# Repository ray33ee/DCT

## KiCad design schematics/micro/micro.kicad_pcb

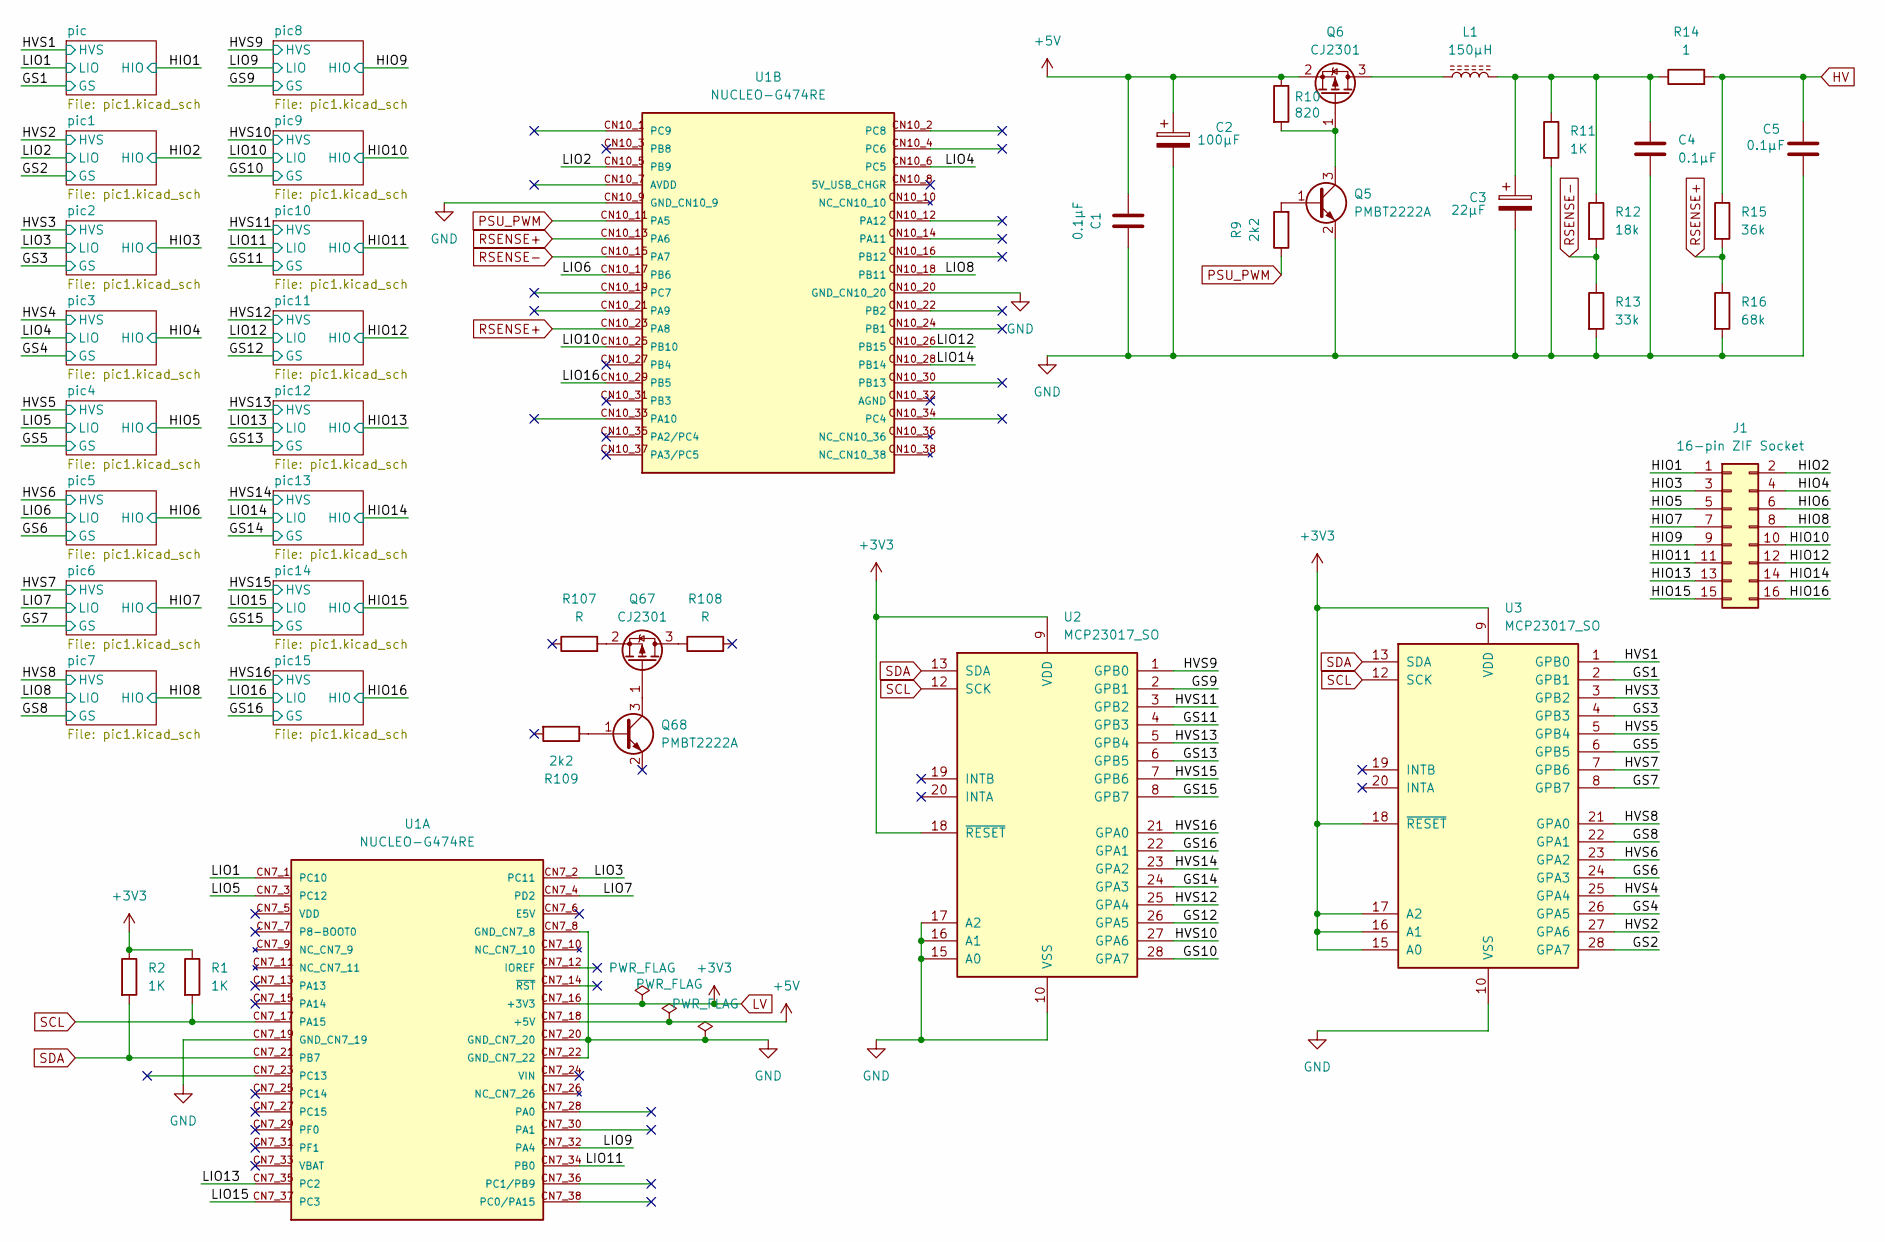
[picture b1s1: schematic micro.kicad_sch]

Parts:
C1, C4, C5: 0.1µF; C_1206_3216Metric_Pad1.33x1.80mm_HandSolder
C2: 100µF; CP_Elec_6.3x7.7
C3: 22µF; CP_Elec_6.3x5.4
J1: 16-pin ZIF Socket; ZIF-16
L1: 150µH; L_Axial_L11.0mm_D4.5mm_P15.24mm_Horizontal_Fastron_MECC
Q5, Q68: PMBT2222A; SOT-23
Q6, Q67: CJ2301; SOT-23
R1, R2, R11: 1K; R_1206_3216Metric_Pad1.30x1.75mm_HandSolder
R9, R109: 2k2; R_1206_3216Metric_Pad1.30x1.75mm_HandSolder
R10: 820; R_1206_3216Metric_Pad1.30x1.75mm_HandSolder
R12: 18k; R_1206_3216Metric_Pad1.30x1.75mm_HandSolder
R13: 33k; R_1206_3216Metric_Pad1.30x1.75mm_HandSolder
R14: 1; R_1206_3216Metric_Pad1.30x1.75mm_HandSolder
R15: 36k; R_1206_3216Metric_Pad1.30x1.75mm_HandSolder
R16: 68k; R_1206_3216Metric_Pad1.30x1.75mm_HandSolder
R107, R108: R; R_1206_3216Metric_Pad1.30x1.75mm_HandSolder
U1: NUCLEO-G474RE; G474; PARTREV 17; DigiKey_Part_Number 497-19491-ND
U2, U3: MCP23017_SO; SOIC-28W_7.5x17.9mm_P1.27mm

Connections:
+5V: C1.2, C2.1, Q6.2 (S), R10.1, U1.CN7_18 (+5V)
/GS1: U3.2 (GPB1); also elsewhere on the board
/GS2: U3.28 (GPA7); also elsewhere on the board
/GS3: U3.4 (GPB3); also elsewhere on the board
/GS4: U3.26 (GPA5); also elsewhere on the board
/GS5: U3.6 (GPB5); also elsewhere on the board
/GS6: U3.24 (GPA3); also elsewhere on the board
/GS7: U3.8 (GPB7); also elsewhere on the board
/GS8: U3.22 (GPA1); also elsewhere on the board
/GS9: U2.2 (GPB1); also elsewhere on the board
/GS10: U2.28 (GPA7); also elsewhere on the board
/GS11: U2.4 (GPB3); also elsewhere on the board
/GS12: U2.26 (GPA5); also elsewhere on the board
/GS13: U2.6 (GPB5); also elsewhere on the board
/GS14: U2.24 (GPA3); also elsewhere on the board
/GS15: U2.8 (GPB7); also elsewhere on the board
/GS16: U2.22 (GPA1); also elsewhere on the board
/HIO1: J1.1; also elsewhere on the board
/HIO2: J1.2; also elsewhere on the board
/HIO3: J1.3; also elsewhere on the board
/HIO4: J1.4; also elsewhere on the board
/HIO5: J1.5; also elsewhere on the board
/HIO6: J1.6; also elsewhere on the board
/HIO7: J1.7; also elsewhere on the board
/HIO8: J1.8; also elsewhere on the board
/HIO9: J1.9; also elsewhere on the board
/HIO10: J1.10; also elsewhere on the board
/HIO11: J1.11; also elsewhere on the board
/HIO12: J1.12; also elsewhere on the board
/HIO13: J1.13; also elsewhere on the board
/HIO14: J1.14; also elsewhere on the board
/HIO15: J1.15; also elsewhere on the board
/HIO16: J1.16; also elsewhere on the board
/HVS1: U3.1 (GPB0); also elsewhere on the board
/HVS2: U3.27 (GPA6); also elsewhere on the board
/HVS3: U3.3 (GPB2); also elsewhere on the board
/HVS4: U3.25 (GPA4); also elsewhere on the board
/HVS5: U3.5 (GPB4); also elsewhere on the board
/HVS6: U3.23 (GPA2); also elsewhere on the board
/HVS7: U3.7 (GPB6); also elsewhere on the board
/HVS8: U3.21 (GPA0); also elsewhere on the board
/HVS9: U2.1 (GPB0); also elsewhere on the board
/HVS10: U2.27 (GPA6); also elsewhere on the board
/HVS11: U2.3 (GPB2); also elsewhere on the board
/HVS12: U2.25 (GPA4); also elsewhere on the board
/HVS13: U2.5 (GPB4); also elsewhere on the board
/HVS14: U2.23 (GPA2); also elsewhere on the board
/HVS15: U2.7 (GPB6); also elsewhere on the board
/HVS16: U2.21 (GPA0); also elsewhere on the board
/LIO1: U1.CN7_1 (PC10); also elsewhere on the board
/LIO2: U1.CN10_5 (PB9); also elsewhere on the board
/LIO3: U1.CN7_2 (PC11); also elsewhere on the board
/LIO4: U1.CN10_6 (PC5); also elsewhere on the board
/LIO5: U1.CN7_3 (PC12); also elsewhere on the board
/LIO6: U1.CN10_17 (PB6); also elsewhere on the board
/LIO7: U1.CN7_4 (PD2); also elsewhere on the board
/LIO8: U1.CN10_18 (PB11); also elsewhere on the board
/LIO9: U1.CN7_32 (PA4); also elsewhere on the board
/LIO10: U1.CN10_25 (PB10); also elsewhere on the board
/LIO11: U1.CN7_34 (PB0); also elsewhere on the board
/LIO12: U1.CN10_26 (PB15); also elsewhere on the board
/LIO13: U1.CN7_35 (PC2); also elsewhere on the board
/LIO14: U1.CN10_28 (PB14); also elsewhere on the board
/LIO15: U1.CN7_37 (PC3); also elsewhere on the board
/LIO16: U1.CN10_29 (PB5); also elsewhere on the board
GND: C1.1, C2.2, C3.2, C4.2, C5.2, Q5.2 (E), R11.2, R13.2, R16.2, U1.CN7_8 (GND_CN7_8), U1.CN7_19 (GND_CN7_19), U1.CN7_20 (GND_CN7_20), U1.CN7_22 (GND_CN7_22), U1.CN10_9 (GND_CN10_9), U1.CN10_20 (GND_CN10_20), U2.10 (VSS), U2.15 (A0), U2.16 (A1), U2.17 (A2), U3.10 (VSS); also elsewhere on the board
HV: C5.1, R14.2, R15.1; also elsewhere on the board
LV: R1.1, R2.1, U1.CN7_16 (+3V3), U2.9 (VDD), U2.18 (~RESET), U3.9 (VDD), U3.15 (A0), U3.16 (A1), U3.17 (A2), U3.18 (~RESET); also elsewhere on the board
unnamed: C3.1, C4.1, L1.2, R11.1, R12.1, R14.1
unnamed: Q5.1 (B), R9.2
unnamed: Q5.3 (C), Q6.1 (G), R10.2
unnamed: L1.1, Q6.3 (D)
unnamed: Q67.3 (D), R108.1
unnamed: Q67.1 (G), Q68.3 (C)
unnamed: Q67.2 (S), R107.2
unnamed: Q68.1 (B), R109.1
PSU_PWM: R9.1, U1.CN10_11 (PA5)
RSENSE+: R15.2, R16.1, U1.CN10_13 (PA6), U1.CN10_23 (PA8)
RSENSE-: R12.2, R13.1, U1.CN10_15 (PA7)
SCL: R1.2, U1.CN7_17 (PA15), U2.12 (SCK), U3.12 (SCK)
SDA: R2.2, U1.CN7_21 (PB7), U2.13 (SDA), U3.13 (SDA)

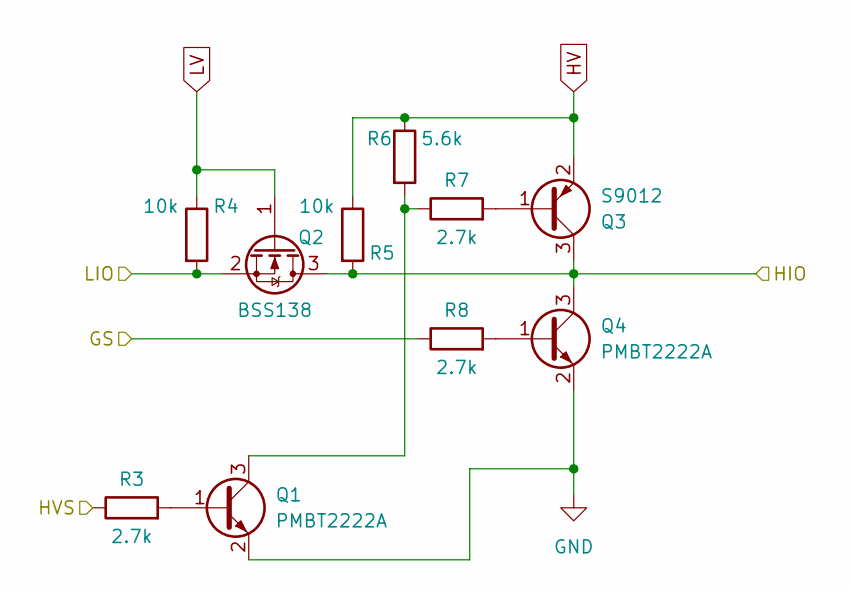
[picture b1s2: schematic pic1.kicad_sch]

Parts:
Q1, Q4: PMBT2222A; SOT-23_Handsoldering
Q2: BSS138; SOT-23_Handsoldering
Q3: S9012; SOT-23_Handsoldering
R3, R7, R8: 2.7k; R_1206_3216Metric_Pad1.30x1.75mm_HandSolder
R4, R5: 10k; R_1206_3216Metric_Pad1.30x1.75mm_HandSolder
R6: 5.6k; R_1206_3216Metric_Pad1.30x1.75mm_HandSolder

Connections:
/GS1: R8.1; also elsewhere on the board
/HIO1: Q2.3 (D), Q3.3 (C), Q4.3 (C), R5.2; also elsewhere on the board
/HVS1: R3.1; also elsewhere on the board
/LIO1: Q2.2 (S), R4.2; also elsewhere on the board
GND: Q1.2 (E), Q4.2 (E); also elsewhere on the board
HV: Q3.2 (E), R5.1, R6.1; also elsewhere on the board
LV: Q2.1 (G), R4.1; also elsewhere on the board
unnamed: Q1.1 (B), R3.2
unnamed: Q1.3 (C), R6.2, R7.1
unnamed: Q3.1 (B), R7.2
unnamed: Q4.1 (B), R8.2

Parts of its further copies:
Q7, Q10, Q11, Q14, Q15, Q18, Q19, Q22, Q23, Q26, Q27, Q30, Q31, Q34, Q35, Q38, Q39, Q42, Q43, Q46, Q47, Q50, Q51, Q54, Q55, Q58, Q59, Q62, Q63, Q66: PMBT2222A; SOT-23_Handsoldering
Q8, Q12, Q16, Q20, Q24, Q28, Q32, Q36, Q40, Q44, Q48, Q52, Q56, Q60, Q64: BSS138; SOT-23_Handsoldering
Q9, Q13, Q17, Q21, Q25, Q29, Q33, Q37, Q41, Q45, Q49, Q53, Q57, Q61, Q65: S9012; SOT-23_Handsoldering
R17, R21, R22, R23, R27, R28, R29, R33, R34, R35, R39, R40, R41, R45, R46, R47, R51, R52, R53, R57, R58, R59, R63, R64, R65, R69, R70, R71, R75, R76, R77, R81, R82, R83, R87, R88, R89, R93, R94, R95, R99, R100, R101, R105, R106: 2.7k; R_1206_3216Metric_Pad1.30x1.75mm_HandSolder
R18, R19, R24, R25, R30, R31, R36, R37, R42, R43, R48, R49, R54, R55, R60, R61, R66, R67, R72, R73, R78, R79, R84, R85, R90, R91, R96, R97, R102, R103: 10k; R_1206_3216Metric_Pad1.30x1.75mm_HandSolder
R20, R26, R32, R38, R44, R50, R56, R62, R68, R74, R80, R86, R92, R98, R104: 5.6k; R_1206_3216Metric_Pad1.30x1.75mm_HandSolder

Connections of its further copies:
/GS2: R22.1; also elsewhere on the board
/GS3: R28.1; also elsewhere on the board
/GS4: R34.1; also elsewhere on the board
/GS5: R40.1; also elsewhere on the board
/GS6: R46.1; also elsewhere on the board
/GS7: R52.1; also elsewhere on the board
/GS8: R58.1; also elsewhere on the board
/GS9: R64.1; also elsewhere on the board
/GS10: R70.1; also elsewhere on the board
/GS11: R76.1; also elsewhere on the board
/GS12: R82.1; also elsewhere on the board
/GS13: R88.1; also elsewhere on the board
/GS14: R94.1; also elsewhere on the board
/GS15: R100.1; also elsewhere on the board
/GS16: R106.1; also elsewhere on the board
/HIO2: Q8.3 (D), Q9.3 (C), Q10.3 (C), R19.2; also elsewhere on the board
/HIO3: Q12.3 (D), Q13.3 (C), Q14.3 (C), R25.2; also elsewhere on the board
/HIO4: Q16.3 (D), Q17.3 (C), Q18.3 (C), R31.2; also elsewhere on the board
/HIO5: Q20.3 (D), Q21.3 (C), Q22.3 (C), R37.2; also elsewhere on the board
/HIO6: Q24.3 (D), Q25.3 (C), Q26.3 (C), R43.2; also elsewhere on the board
/HIO7: Q28.3 (D), Q29.3 (C), Q30.3 (C), R49.2; also elsewhere on the board
/HIO8: Q32.3 (D), Q33.3 (C), Q34.3 (C), R55.2; also elsewhere on the board
/HIO9: Q36.3 (D), Q37.3 (C), Q38.3 (C), R61.2; also elsewhere on the board
/HIO10: Q40.3 (D), Q41.3 (C), Q42.3 (C), R67.2; also elsewhere on the board
/HIO11: Q44.3 (D), Q45.3 (C), Q46.3 (C), R73.2; also elsewhere on the board
/HIO12: Q48.3 (D), Q49.3 (C), Q50.3 (C), R79.2; also elsewhere on the board
/HIO13: Q52.3 (D), Q53.3 (C), Q54.3 (C), R85.2; also elsewhere on the board
/HIO14: Q56.3 (D), Q57.3 (C), Q58.3 (C), R91.2; also elsewhere on the board
/HIO15: Q60.3 (D), Q61.3 (C), Q62.3 (C), R97.2; also elsewhere on the board
/HIO16: Q64.3 (D), Q65.3 (C), Q66.3 (C), R103.2; also elsewhere on the board
/HVS2: R17.1; also elsewhere on the board
/HVS3: R23.1; also elsewhere on the board
/HVS4: R29.1; also elsewhere on the board
/HVS5: R35.1; also elsewhere on the board
/HVS6: R41.1; also elsewhere on the board
/HVS7: R47.1; also elsewhere on the board
/HVS8: R53.1; also elsewhere on the board
/HVS9: R59.1; also elsewhere on the board
/HVS10: R65.1; also elsewhere on the board
/HVS11: R71.1; also elsewhere on the board
/HVS12: R77.1; also elsewhere on the board
/HVS13: R83.1; also elsewhere on the board
/HVS14: R89.1; also elsewhere on the board
/HVS15: R95.1; also elsewhere on the board
/HVS16: R101.1; also elsewhere on the board
/LIO2: Q8.2 (S), R18.2; also elsewhere on the board
/LIO3: Q12.2 (S), R24.2; also elsewhere on the board
/LIO4: Q16.2 (S), R30.2; also elsewhere on the board
/LIO5: Q20.2 (S), R36.2; also elsewhere on the board
/LIO6: Q24.2 (S), R42.2; also elsewhere on the board
/LIO7: Q28.2 (S), R48.2; also elsewhere on the board
/LIO8: Q32.2 (S), R54.2; also elsewhere on the board
/LIO9: Q36.2 (S), R60.2; also elsewhere on the board
/LIO10: Q40.2 (S), R66.2; also elsewhere on the board
/LIO11: Q44.2 (S), R72.2; also elsewhere on the board
/LIO12: Q48.2 (S), R78.2; also elsewhere on the board
/LIO13: Q52.2 (S), R84.2; also elsewhere on the board
/LIO14: Q56.2 (S), R90.2; also elsewhere on the board
/LIO15: Q60.2 (S), R96.2; also elsewhere on the board
/LIO16: Q64.2 (S), R102.2; also elsewhere on the board
GND: Q7.2 (E), Q10.2 (E), Q11.2 (E), Q14.2 (E), Q15.2 (E), Q18.2 (E), Q19.2 (E), Q22.2 (E), Q23.2 (E), Q26.2 (E), Q27.2 (E), Q30.2 (E), Q31.2 (E), Q34.2 (E), Q35.2 (E), Q38.2 (E), Q39.2 (E), Q42.2 (E), Q43.2 (E), Q46.2 (E), Q47.2 (E), Q50.2 (E), Q51.2 (E), Q54.2 (E), Q55.2 (E), Q58.2 (E), Q59.2 (E), Q62.2 (E), Q63.2 (E), Q66.2 (E); also elsewhere on the board
HV: Q9.2 (E), Q13.2 (E), Q17.2 (E), Q21.2 (E), Q25.2 (E), Q29.2 (E), Q33.2 (E), Q37.2 (E), Q41.2 (E), Q45.2 (E), Q49.2 (E), Q53.2 (E), Q57.2 (E), Q61.2 (E), Q65.2 (E), R19.1, R20.1, R25.1, R26.1, R31.1, R32.1, R37.1, R38.1, R43.1, R44.1, R49.1, R50.1, R55.1, R56.1, R61.1, R62.1, R67.1, R68.1, R73.1, R74.1, R79.1, R80.1, R85.1, R86.1, R91.1, R92.1, R97.1, R98.1, R103.1, R104.1; also elsewhere on the board
LV: Q8.1 (G), Q12.1 (G), Q16.1 (G), Q20.1 (G), Q24.1 (G), Q28.1 (G), Q32.1 (G), Q36.1 (G), Q40.1 (G), Q44.1 (G), Q48.1 (G), Q52.1 (G), Q56.1 (G), Q60.1 (G), Q64.1 (G), R18.1, R24.1, R30.1, R36.1, R42.1, R48.1, R54.1, R60.1, R66.1, R72.1, R78.1, R84.1, R90.1, R96.1, R102.1; also elsewhere on the board
unnamed: Q7.1 (B), R17.2
unnamed: Q7.3 (C), R20.2, R21.1
unnamed: Q9.1 (B), R21.2
unnamed: Q10.1 (B), R22.2
unnamed: Q11.1 (B), R23.2
unnamed: Q11.3 (C), R26.2, R27.1
unnamed: Q13.1 (B), R27.2
unnamed: Q14.1 (B), R28.2
unnamed: Q15.1 (B), R29.2
unnamed: Q15.3 (C), R32.2, R33.1
unnamed: Q17.1 (B), R33.2
unnamed: Q18.1 (B), R34.2
unnamed: Q19.1 (B), R35.2
unnamed: Q19.3 (C), R38.2, R39.1
unnamed: Q21.1 (B), R39.2
unnamed: Q22.1 (B), R40.2
unnamed: Q23.1 (B), R41.2
unnamed: Q23.3 (C), R44.2, R45.1
unnamed: Q25.1 (B), R45.2
unnamed: Q26.1 (B), R46.2
unnamed: Q27.1 (B), R47.2
unnamed: Q27.3 (C), R50.2, R51.1
unnamed: Q29.1 (B), R51.2
unnamed: Q30.1 (B), R52.2
unnamed: Q31.1 (B), R53.2
unnamed: Q31.3 (C), R56.2, R57.1
unnamed: Q33.1 (B), R57.2
unnamed: Q34.1 (B), R58.2
unnamed: Q35.1 (B), R59.2
unnamed: Q35.3 (C), R62.2, R63.1
unnamed: Q37.1 (B), R63.2
unnamed: Q38.1 (B), R64.2
unnamed: Q39.1 (B), R65.2
unnamed: Q39.3 (C), R68.2, R69.1
unnamed: Q41.1 (B), R69.2
unnamed: Q42.1 (B), R70.2
unnamed: Q43.1 (B), R71.2
unnamed: Q43.3 (C), R74.2, R75.1
unnamed: Q45.1 (B), R75.2
unnamed: Q46.1 (B), R76.2
unnamed: Q47.1 (B), R77.2
unnamed: Q47.3 (C), R80.2, R81.1
unnamed: Q49.1 (B), R81.2
unnamed: Q50.1 (B), R82.2
unnamed: Q51.1 (B), R83.2
unnamed: Q51.3 (C), R86.2, R87.1
unnamed: Q53.1 (B), R87.2
unnamed: Q54.1 (B), R88.2
unnamed: Q55.1 (B), R89.2
unnamed: Q55.3 (C), R92.2, R93.1
unnamed: Q57.1 (B), R93.2
unnamed: Q58.1 (B), R94.2
unnamed: Q59.1 (B), R95.2
unnamed: Q59.3 (C), R98.2, R99.1
unnamed: Q61.1 (B), R99.2
unnamed: Q62.1 (B), R100.2
unnamed: Q63.1 (B), R101.2
unnamed: Q63.3 (C), R104.2, R105.1
unnamed: Q65.1 (B), R105.2
unnamed: Q66.1 (B), R106.2

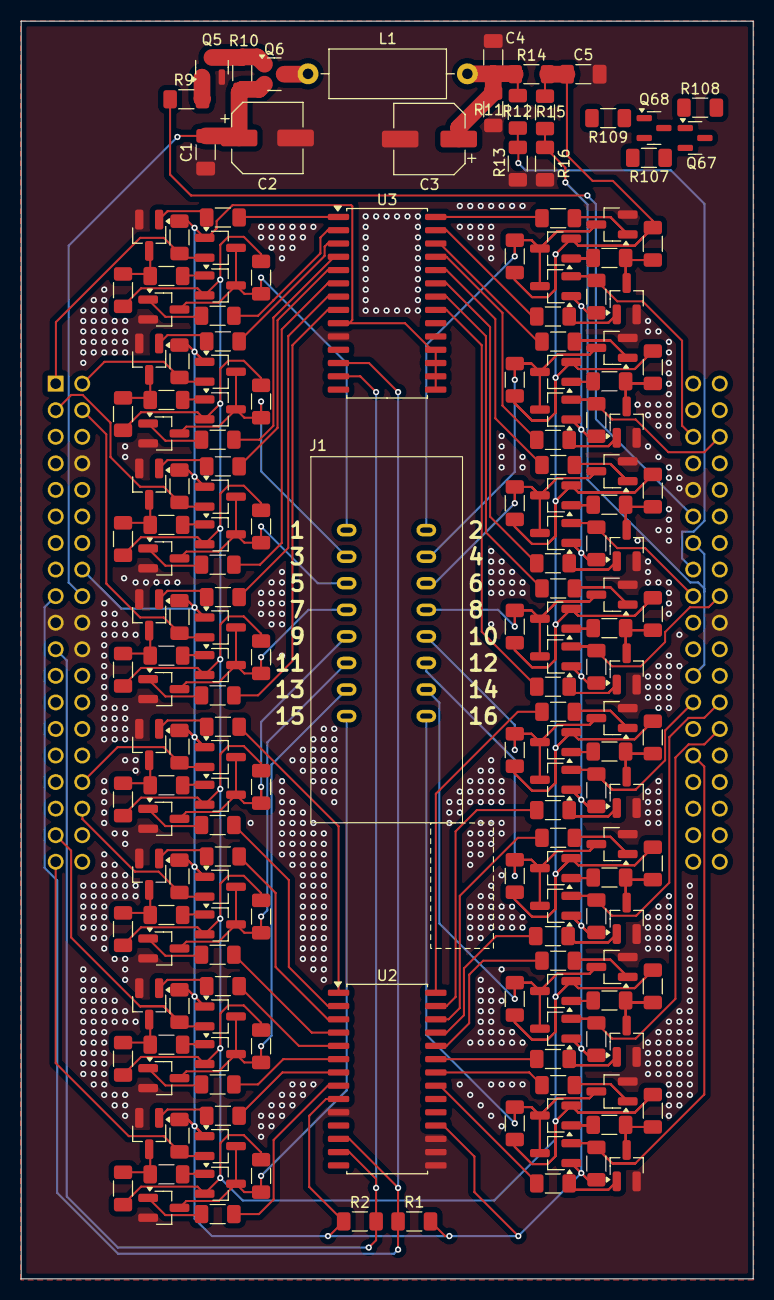
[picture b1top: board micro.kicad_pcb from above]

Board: 2 copper layers, 70.0 x 120.3 mm, 187 parts (0 on the bottom side), 145 nets.

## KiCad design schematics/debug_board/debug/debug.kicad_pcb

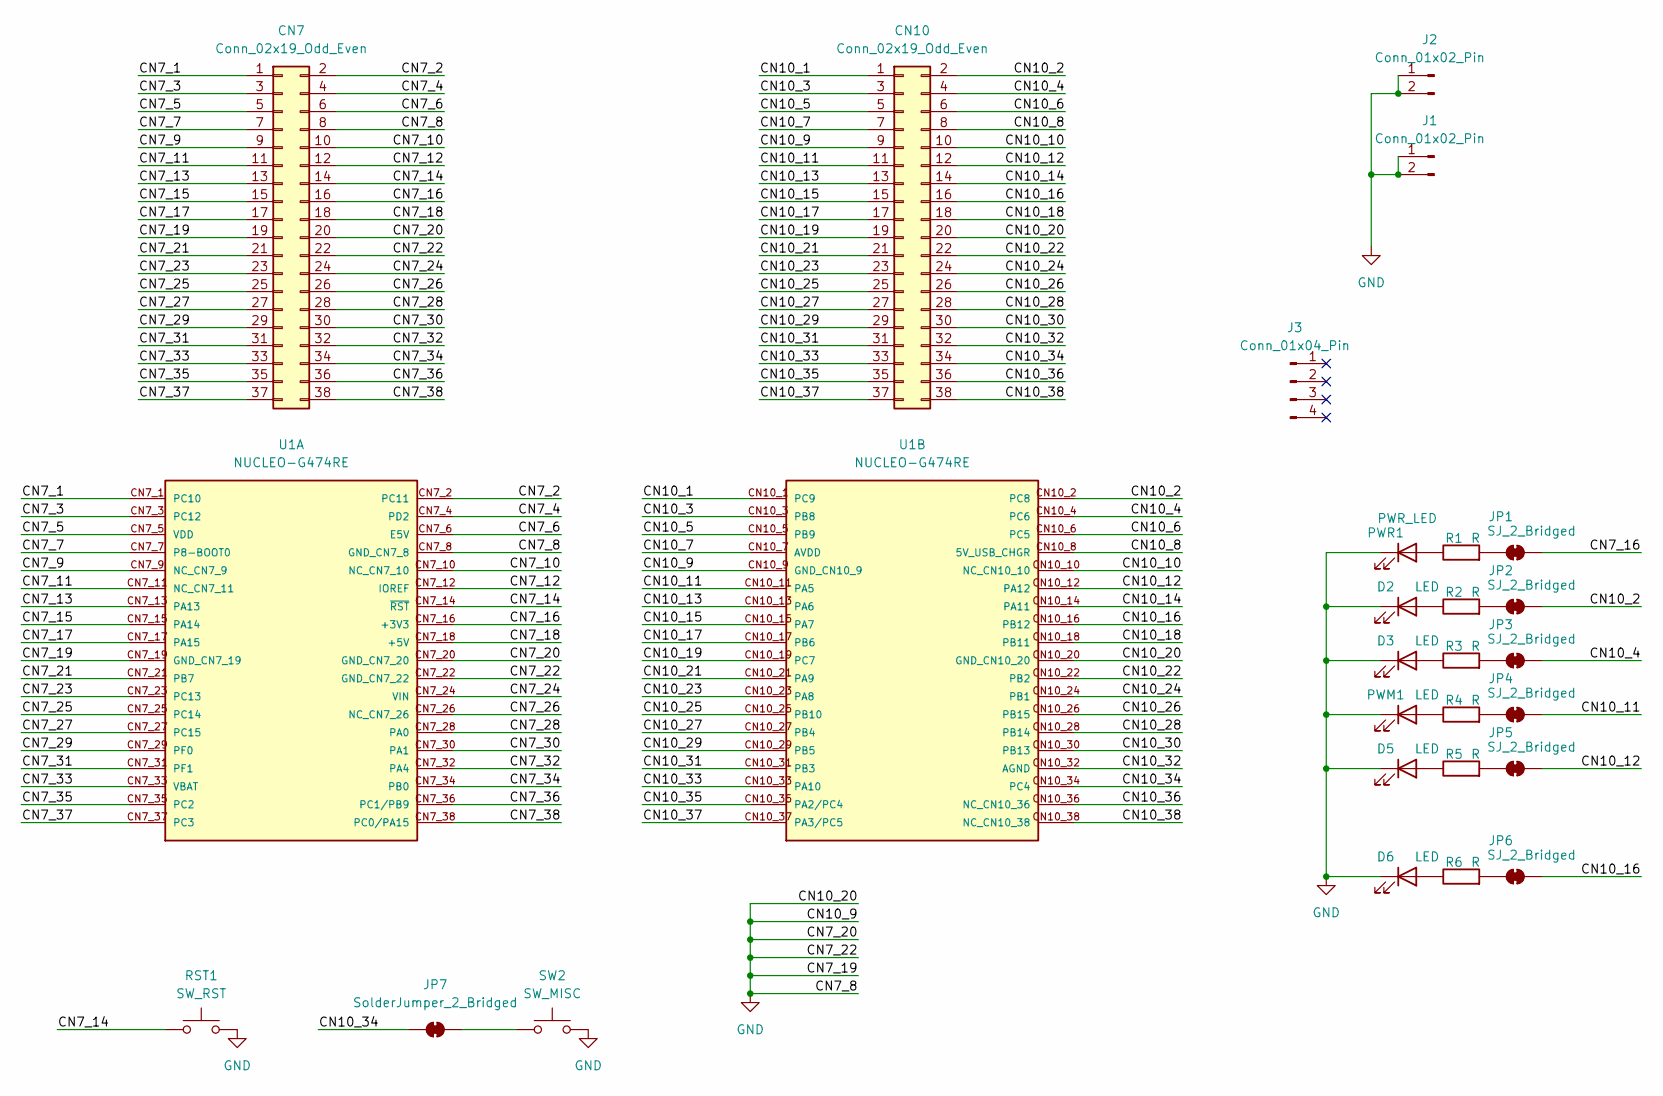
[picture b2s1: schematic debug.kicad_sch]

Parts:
CN7, CN10: Conn_02x19_Odd_Even; PinHeader_2x19_P2.54mm_Vertical
D2, D3, D5, D6: LED; LED_1206_3216Metric_Pad1.42x1.75mm_HandSolder
J1, J2: Conn_01x02_Pin; PinHeader_2x01_P2.54mm_Vertical
J3: Conn_01x04_Pin; PinHeader_1x04_P2.54mm_Vertical
JP1, JP2, JP3, JP4, JP5, JP6: SJ_2_Bridged; SolderJumper-2_P1.3mm_Bridged_RoundedPad1.0x1.5mm
JP7: SolderJumper_2_Bridged; SolderJumper-2_P1.3mm_Bridged_RoundedPad1.0x1.5mm
PWM1: LED; LED_1206_3216Metric_Pad1.42x1.75mm_HandSolder
PWR1: PWR_LED; LED_1206_3216Metric_Pad1.42x1.75mm_HandSolder
R1, R2, R3, R4, R5, R6: R; R_1206_3216Metric_Pad1.30x1.75mm_HandSolder
RST1: SW_RST; SW_SPST_FSMSM
SW2: SW_MISC; SW_SPST_FSMSM
U1: NUCLEO-G474RE; G474; PARTREV 17; DigiKey_Part_Number 497-19491-ND

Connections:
/CN7_1: CN7.1, U1.CN7_1 (PC10)
/CN7_2: CN7.2, U1.CN7_2 (PC11)
/CN7_3: CN7.3, U1.CN7_3 (PC12)
/CN7_4: CN7.4, U1.CN7_4 (PD2)
/CN7_5: CN7.5, U1.CN7_5 (VDD)
/CN7_6: CN7.6, U1.CN7_6 (E5V)
/CN7_7: CN7.7, U1.CN7_7 (P8-BOOT0)
/CN7_9: CN7.9, U1.CN7_9 (NC_CN7_9)
/CN7_10: CN7.10, U1.CN7_10 (NC_CN7_10)
/CN7_11: CN7.11, U1.CN7_11 (NC_CN7_11)
/CN7_12: CN7.12, U1.CN7_12 (IOREF)
/CN7_13: CN7.13, U1.CN7_13 (PA13)
/CN7_14: CN7.14, RST1.1, U1.CN7_14 (~RST)
/CN7_15: CN7.15, U1.CN7_15 (PA14)
/CN7_16: CN7.16, JP1.2 (B), U1.CN7_16 (+3V3)
/CN7_17: CN7.17, U1.CN7_17 (PA15)
/CN7_18: CN7.18, U1.CN7_18 (+5V)
/CN7_21: CN7.21, U1.CN7_21 (PB7)
/CN7_23: CN7.23, U1.CN7_23 (PC13)
/CN7_24: CN7.24, U1.CN7_24 (VIN)
/CN7_25: CN7.25, U1.CN7_25 (PC14)
/CN7_26: CN7.26, U1.CN7_26 (NC_CN7_26)
/CN7_27: CN7.27, U1.CN7_27 (PC15)
/CN7_28: CN7.28, U1.CN7_28 (PA0)
/CN7_29: CN7.29, U1.CN7_29 (PF0)
/CN7_30: CN7.30, U1.CN7_30 (PA1)
/CN7_31: CN7.31, U1.CN7_31 (PF1)
/CN7_32: CN7.32, U1.CN7_32 (PA4)
/CN7_33: CN7.33, U1.CN7_33 (VBAT)
/CN7_34: CN7.34, U1.CN7_34 (PB0)
/CN7_35: CN7.35, U1.CN7_35 (PC2)
/CN7_36: CN7.36, U1.CN7_36 (PC1/PB9)
/CN7_37: CN7.37, U1.CN7_37 (PC3)
/CN7_38: CN7.38, U1.CN7_38 (PC0/PA15)
/CN10_1: CN10.1, U1.CN10_1 (PC9)
/CN10_2: CN10.2, JP2.2 (B), U1.CN10_2 (PC8)
/CN10_3: CN10.3, U1.CN10_3 (PB8)
/CN10_4: CN10.4, JP3.2 (B), U1.CN10_4 (PC6)
/CN10_5: CN10.5, U1.CN10_5 (PB9)
/CN10_6: CN10.6, U1.CN10_6 (PC5)
/CN10_7: CN10.7, U1.CN10_7 (AVDD)
/CN10_8: CN10.8, U1.CN10_8 (5V_USB_CHGR)
/CN10_10: CN10.10, U1.CN10_10 (NC_CN10_10)
/CN10_11: CN10.11, JP4.2 (B), U1.CN10_11 (PA5)
/CN10_12: CN10.12, JP5.2 (B), U1.CN10_12 (PA12)
/CN10_13: CN10.13, U1.CN10_13 (PA6)
/CN10_14: CN10.14, U1.CN10_14 (PA11)
/CN10_15: CN10.15, U1.CN10_15 (PA7)
/CN10_16: CN10.16, JP6.2 (B), U1.CN10_16 (PB12)
/CN10_17: CN10.17, U1.CN10_17 (PB6)
/CN10_18: CN10.18, U1.CN10_18 (PB11)
/CN10_19: CN10.19, U1.CN10_19 (PC7)
/CN10_21: CN10.21, U1.CN10_21 (PA9)
/CN10_22: CN10.22, U1.CN10_22 (PB2)
/CN10_23: CN10.23, U1.CN10_23 (PA8)
/CN10_24: CN10.24, U1.CN10_24 (PB1)
/CN10_25: CN10.25, U1.CN10_25 (PB10)
/CN10_26: CN10.26, U1.CN10_26 (PB15)
/CN10_27: CN10.27, U1.CN10_27 (PB4)
/CN10_28: CN10.28, U1.CN10_28 (PB14)
/CN10_29: CN10.29, U1.CN10_29 (PB5)
/CN10_30: CN10.30, U1.CN10_30 (PB13)
/CN10_31: CN10.31, U1.CN10_31 (PB3)
/CN10_32: CN10.32, U1.CN10_32 (AGND)
/CN10_33: CN10.33, U1.CN10_33 (PA10)
/CN10_34: CN10.34, JP7.1 (A), U1.CN10_34 (PC4)
/CN10_35: CN10.35, U1.CN10_35 (PA2/PC4)
/CN10_36: CN10.36, U1.CN10_36 (NC_CN10_36)
/CN10_37: CN10.37, U1.CN10_37 (PA3/PC5)
/CN10_38: CN10.38, U1.CN10_38 (NC_CN10_38)
GND: CN7.8, CN7.19, CN7.20, CN7.22, CN10.9, CN10.20, D2.1 (K), D3.1 (K), D5.1 (K), D6.1 (K), J1.1, J1.2, J2.1, J2.2, PWM1.1 (K), PWR1.1 (K), RST1.2, SW2.2, U1.CN7_8 (GND_CN7_8), U1.CN7_19 (GND_CN7_19), U1.CN7_20 (GND_CN7_20), U1.CN7_22 (GND_CN7_22), U1.CN10_9 (GND_CN10_9), U1.CN10_20 (GND_CN10_20)
unnamed: D2.2 (A), R2.1
unnamed: D3.2 (A), R3.1
unnamed: D5.2 (A), R5.1
unnamed: D6.2 (A), R6.1
unnamed: JP1.1 (A), R1.2
unnamed: JP2.1 (A), R2.2
unnamed: JP3.1 (A), R3.2
unnamed: JP4.1 (A), R4.2
unnamed: JP5.1 (A), R5.2
unnamed: JP6.1 (A), R6.2
unnamed: JP7.2 (B), SW2.1
unnamed: PWM1.2 (A), R4.1
unnamed: PWR1.2 (A), R1.1

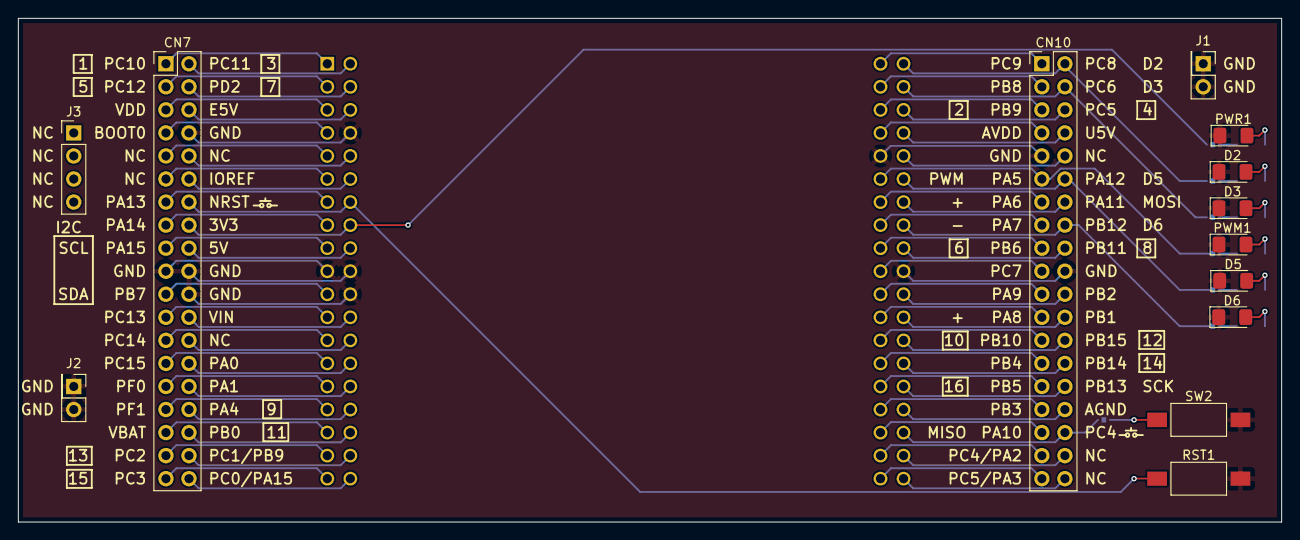
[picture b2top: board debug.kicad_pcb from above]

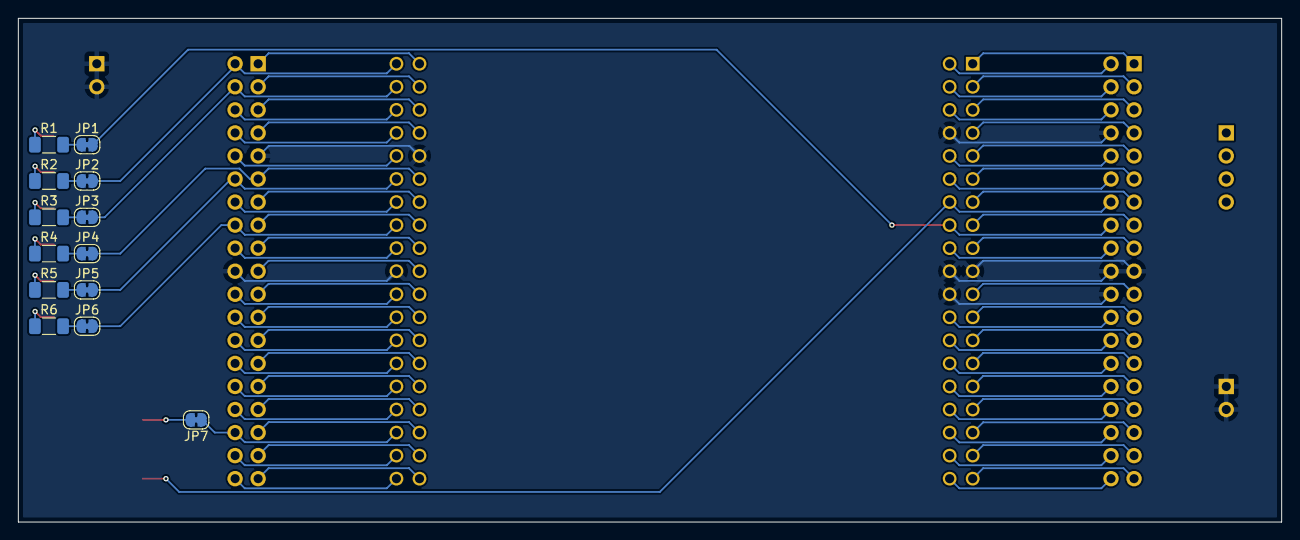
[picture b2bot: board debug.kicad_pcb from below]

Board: 2 copper layers, 139.2 x 55.5 mm, 27 parts (13 on the bottom side), 84 nets.

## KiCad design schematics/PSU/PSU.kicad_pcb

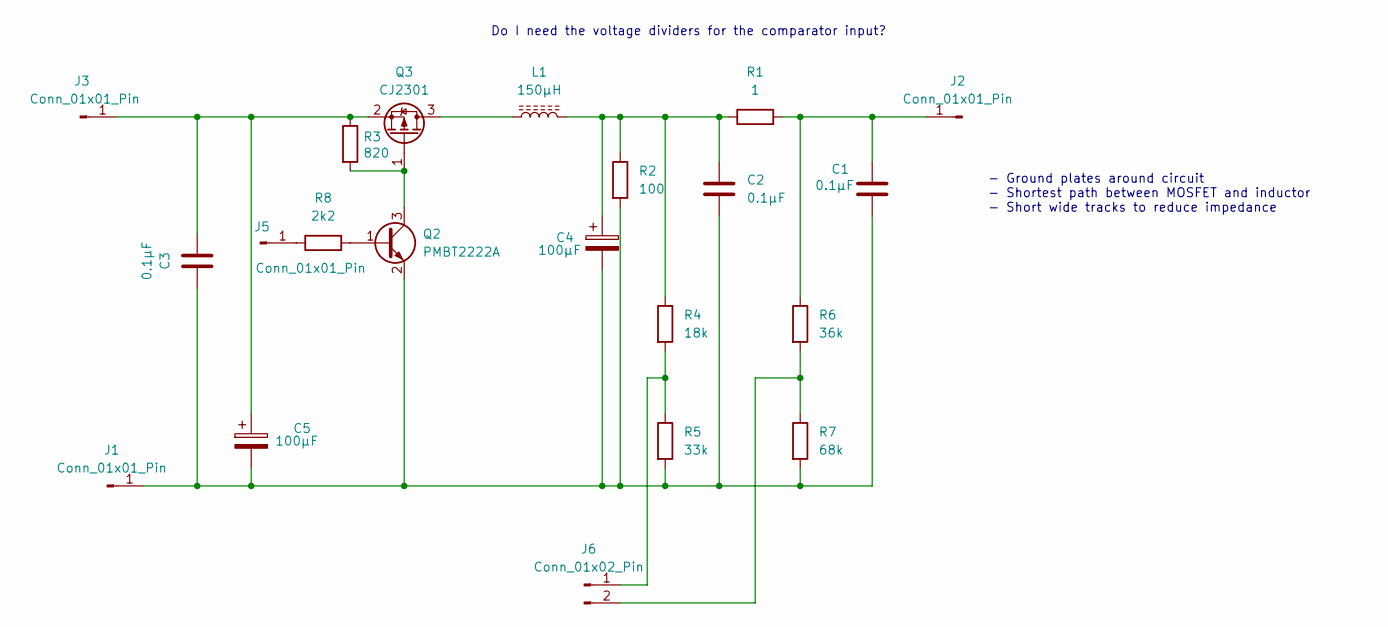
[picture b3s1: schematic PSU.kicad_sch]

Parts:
C1, C2, C3: 0.1µF; C_1206_3216Metric_Pad1.33x1.80mm_HandSolder
C4, C5: 100µF; CP_Radial_D10.0mm_P5.00mm
J1, J2, J3, J5: Conn_01x01_Pin; PinHeader_1x01_P2.54mm_Vertical
J6: Conn_01x02_Pin; PinHeader_1x02_P2.54mm_Vertical
L1: 150µH; L_Axial_L11.0mm_D4.5mm_P15.24mm_Horizontal_Fastron_MECC
Q2: PMBT2222A; SOT-23
Q3: CJ2301; SOT-23
R1: 1; R_1206_3216Metric_Pad1.30x1.75mm_HandSolder
R2: 100; R_2512_6332Metric_Pad1.40x3.35mm_HandSolder
R3: 820; R_1206_3216Metric_Pad1.30x1.75mm_HandSolder
R4: 18k; R_1206_3216Metric_Pad1.30x1.75mm_HandSolder
R5: 33k; R_1206_3216Metric_Pad1.30x1.75mm_HandSolder
R6: 36k; R_1206_3216Metric_Pad1.30x1.75mm_HandSolder
R7: 68k; R_1206_3216Metric_Pad1.30x1.75mm_HandSolder
R8: 2k2; R_1206_3216Metric_Pad1.30x1.75mm_HandSolder

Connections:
unnamed: C2.1, C4.1, L1.2, R1.1, R2.1, R4.1
unnamed: C1.2, C2.2, C3.1, C4.2, C5.2, J1.1, Q2.2 (E), R2.2, R5.2, R7.2
unnamed: C1.1, J2.1, R1.2, R6.1
unnamed: C3.2, C5.1, J3.1, Q3.2 (S), R3.1
unnamed: J5.1, R8.1
unnamed: J6.1, R4.2, R5.1
unnamed: J6.2, R6.2, R7.1
unnamed: Q2.1 (B), R8.2
unnamed: Q2.3 (C), Q3.1 (G), R3.2
unnamed: L1.1, Q3.3 (D)

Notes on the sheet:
- Ground plates around circuit - Shortest path between MOSFET and inductor - Short wide tracks to reduce impedance
Do I need the voltage dividers for the comparator input?

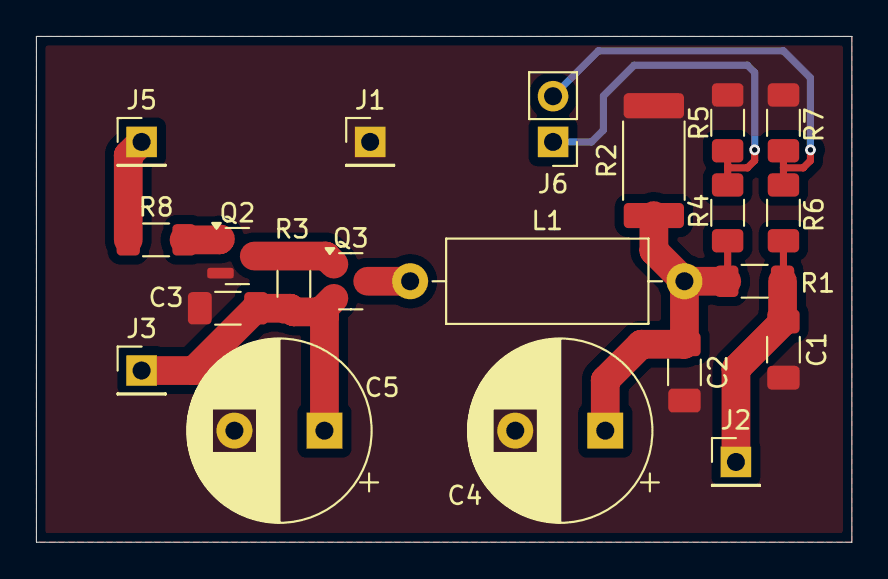
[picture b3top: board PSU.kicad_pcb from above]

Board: 2 copper layers, 45.3 x 28.1 mm, 21 parts (0 on the bottom side), 10 nets.

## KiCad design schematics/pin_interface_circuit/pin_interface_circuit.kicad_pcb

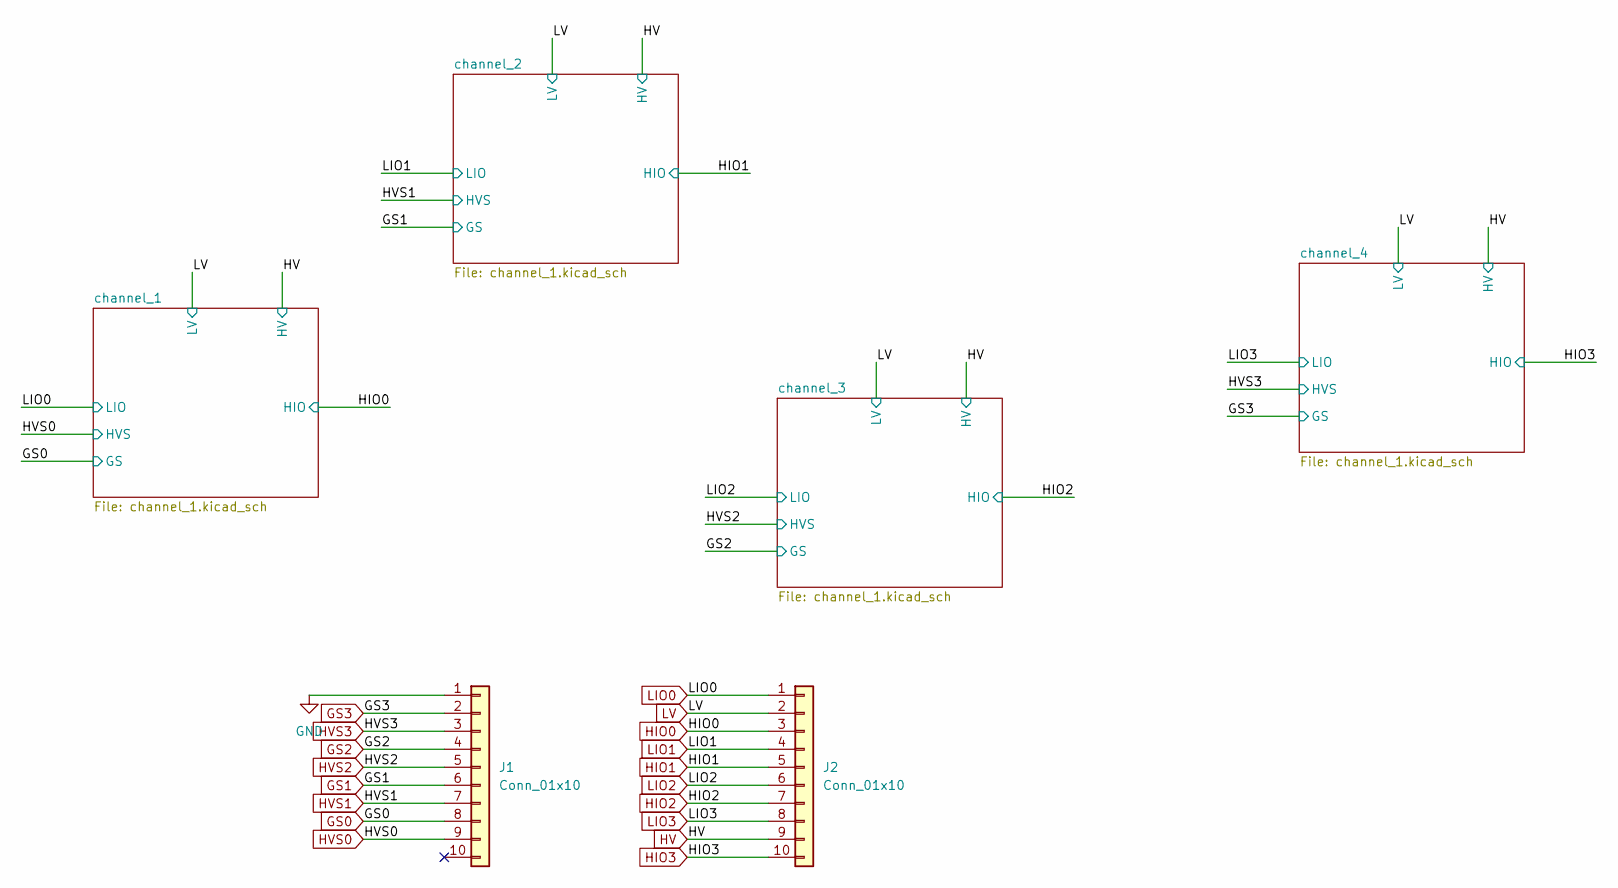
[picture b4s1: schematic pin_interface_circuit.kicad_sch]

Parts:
J1, J2: Conn_01x10; PinHeader_1x10_P2.54mm_Vertical

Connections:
GND: J1.1; also elsewhere on the board
GS0: J1.8; also elsewhere on the board
GS1: J1.6; also elsewhere on the board
GS2: J1.4; also elsewhere on the board
GS3: J1.2; also elsewhere on the board
HIO0: J2.3; also elsewhere on the board
HIO1: J2.5; also elsewhere on the board
HIO2: J2.7; also elsewhere on the board
HIO3: J2.10; also elsewhere on the board
HV: J2.9; also elsewhere on the board
HVS0: J1.9; also elsewhere on the board
HVS1: J1.7; also elsewhere on the board
HVS2: J1.5; also elsewhere on the board
HVS3: J1.3; also elsewhere on the board
LIO0: J2.1; also elsewhere on the board
LIO1: J2.4; also elsewhere on the board
LIO2: J2.6; also elsewhere on the board
LIO3: J2.8; also elsewhere on the board
LV: J2.2; also elsewhere on the board

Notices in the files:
microDCT/Core/Src/stm32g4xx_hal_msp.c:
Copyright (c) 2024 STMicroelectronics.
All rights reserved.
This software is licensed under terms that can be found in the LICENSE file
